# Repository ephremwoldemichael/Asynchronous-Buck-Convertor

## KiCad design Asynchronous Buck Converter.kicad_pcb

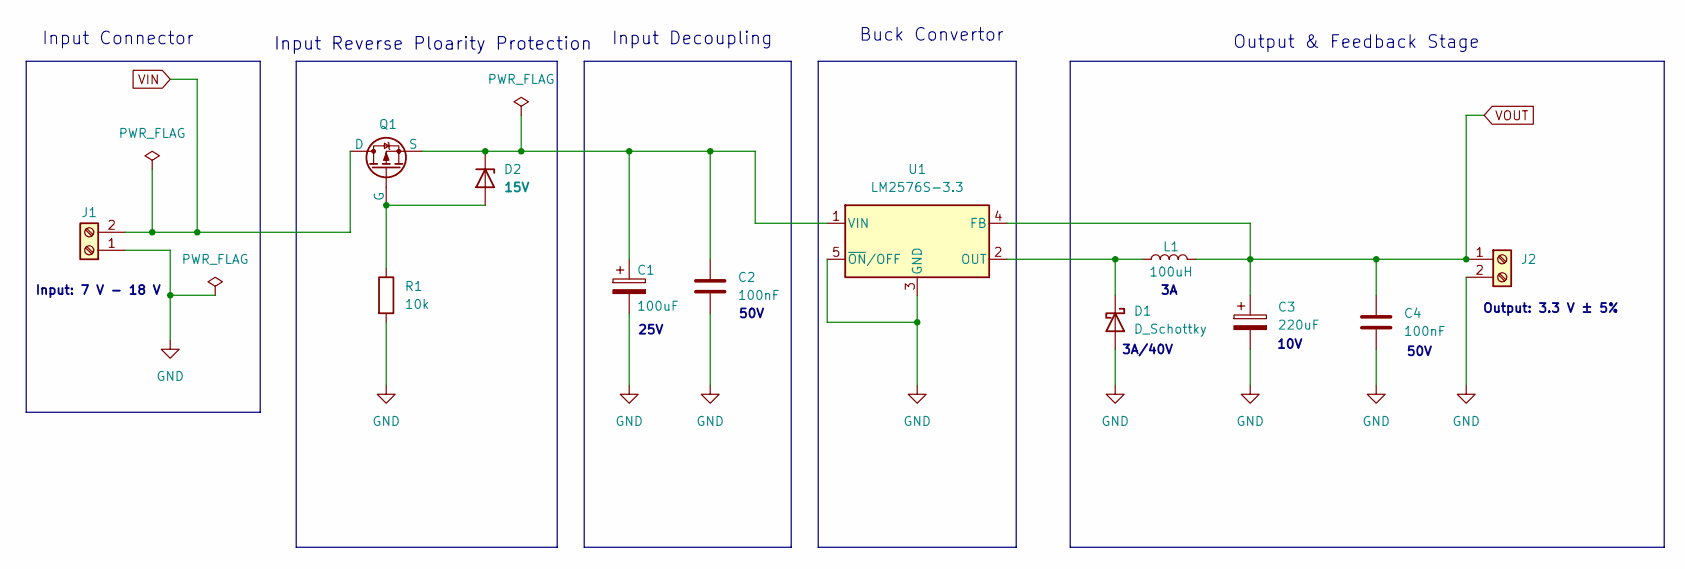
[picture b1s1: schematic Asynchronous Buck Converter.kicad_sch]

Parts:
C1: 100uF; CP_Elec_6.3x5.4; MPN UWT1E101MCL1GS
C2, C4: 100nF; C_0603_1608Metric; MPN GRM188R71H104KA93D
C3: 220uF; CP_Elec_8x6.5; MPN UWT1A221MCL1GS
D1: D_Schottky; D_SMA; MPN SS34-E3/61T
D2: 15V; SOT-23; MPN BZX84C15LT1G
J1, J2: Screw_Terminal_01x02; TerminalBlock_Phoenix_PT-1,5-2-5.0-H_1x02_P5.00mm_Horizontal; MPN 1935776
L1: 100uH; L_Bourns_SRF1260; MPN MSS1260T-104MLB
Q1: PMOS; SOT-23; MPN DMP3098L-7
R1: 10k; R_0402_1005Metric; MPN RC0402FR-0710KL
U1: LM2576S-3.3; TO-263-5_TabPin3; MPN LM2576S-3.3/NOPB

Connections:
GND: C1.2, C2.2, C3.2, C4.2, D1.2 (A), J1.1, J2.2, R1.2, U1.3 (GND), U1.5 (~ON/OFF)
unnamed: D1.1 (K), L1.1, U1.2 (OUT)
unnamed: D2.2 (A), Q1.2 (G), R1.1
unnamed: C1.1, C2.1, D2.1 (K), Q1.3 (S), U1.1 (VIN)
VIN: J1.2, Q1.1 (D)
VOUT: C3.1, C4.1, J2.1, L1.2, U1.4 (FB)

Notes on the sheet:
Input Reverse Ploarity Protection
50V
Input: 7 V - 18 V
Input Decoupling
Output: 3.3 V ± 5%
10V
25V
Input Connector
Buck Convertor
3A/40V
Output & Feedback Stage
50V

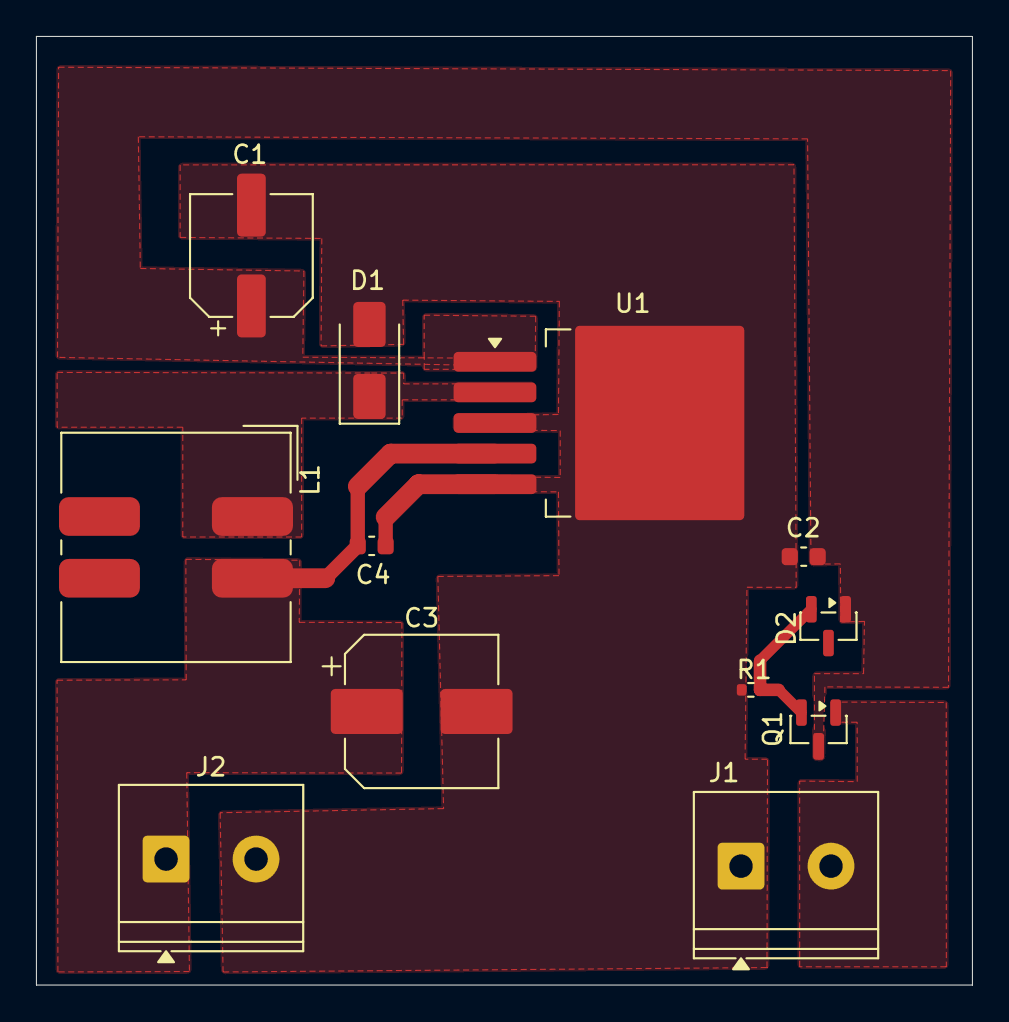
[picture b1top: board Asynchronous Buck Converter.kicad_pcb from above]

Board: 2 copper layers, 52.0 x 52.7 mm, 12 parts (0 on the bottom side), 6 nets.
